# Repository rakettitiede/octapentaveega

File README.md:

# OctaPentaVeega

Fun hobby project to generate 32 x 16 characters of text on VGA output (or alternatively 64x64 pixel graphics, or split-screen graphics/text) from Attiny85 with 6x10 pixel font.

Data is read from UART at 9600bps. [Subset of ANSI escapes is supported](https://github.com/Jartza/octapentaveega/blob/master/vga_uart_protocol.txt).

Wiring 3 Attinys together gets you 8 color output :)

Links:
* <a href="https://www.youtube.com/watch?v=G1QWNDck0yU" target="_blank">Video: Ansi tester 8-color (ansitester.py)</a>
* <a href="https://www.youtube.com/watch?v=Vw5xGuLFy8Q" target="_blank">Video: Ansi tester Black & White (ansitester.py)</a>
* <a href="https://www.youtube.com/watch?v=YL0RwEtTN70" target="_blank">Video: Graphics mode (tricoder) & left scroll</a>
* <a href="https://www.youtube.com/watch?v=1iC2AHI5caI" target="_blank">Video: Full screen scroll (B/W)</a>
* <a href="https://www.youtube.com/watch?v=936m7FMS__c" target="_blank">Video: Full screen scroll (8-color)</a>
* <a href="https://drive.google.com/file/d/0B2dTzW9TMeBxN29YOVFsZFJ2Sm8/view?usp=sharing&resourcekey=0-qg94SZRgscnID9sQj7wqgg" target="_blank">Video: Multiple individual rows scroll (B/W)</a>
* <a href="https://drive.google.com/file/d/0B2dTzW9TMeBxQ1luNFhwcXl3QjA/view?usp=sharing&resourcekey=0-P5mUCc9mNvyFCUTxm9JVWQ" target="_blank">Picture: 6x10 pixel font</a>
* <a href="https://drive.google.com/file/d/0B2dTzW9TMeBxRzJOQVZMNFE0STg/view?usp=sharing&resourcekey=0-tbPVQ-RSZv2ljsOSo7lrrg" target="_blank">Picture: Generic (B/W)</a>

Board photos:
* <a href="https://drive.google.com/file/d/0B2dTzW9TMeBxaFFxam1uVW05NlE/view?usp=sharing&resourcekey=0-hj-EZfwC4E2AGv0eFjva1Q" target="_blank">B/W board</a>
* <a href="https://drive.google.com/file/d/0B2dTzW9TMeBxRXVzSUNCT1h2NHM/view?usp=sharing&resourcekey=0-VIRaT1kCkgjpB7zByPp_LA" target="_blank">8-color board</a>
* <a href="https://drive.google.com/file/d/0B2dTzW9TMeBxX2VmQmw3aXhWUDA/view?usp=sharing&resourcekey=0-ecXRcLez51cEmPnjZG1DXQ" target="_blank">8-color board back</a>
* <a href="https://drive.google.com/file/d/0B2dTzW9TMeBxUDQ4QUduWDV2TFE/view?usp=sharing&resourcekey=0-0n-sL1mumwSXGCBFCg1Kcg" target="_blank">Arduino shield, 8-color with level shifter (3.3 / 5v compatible)</a>

<p>

//Jartza

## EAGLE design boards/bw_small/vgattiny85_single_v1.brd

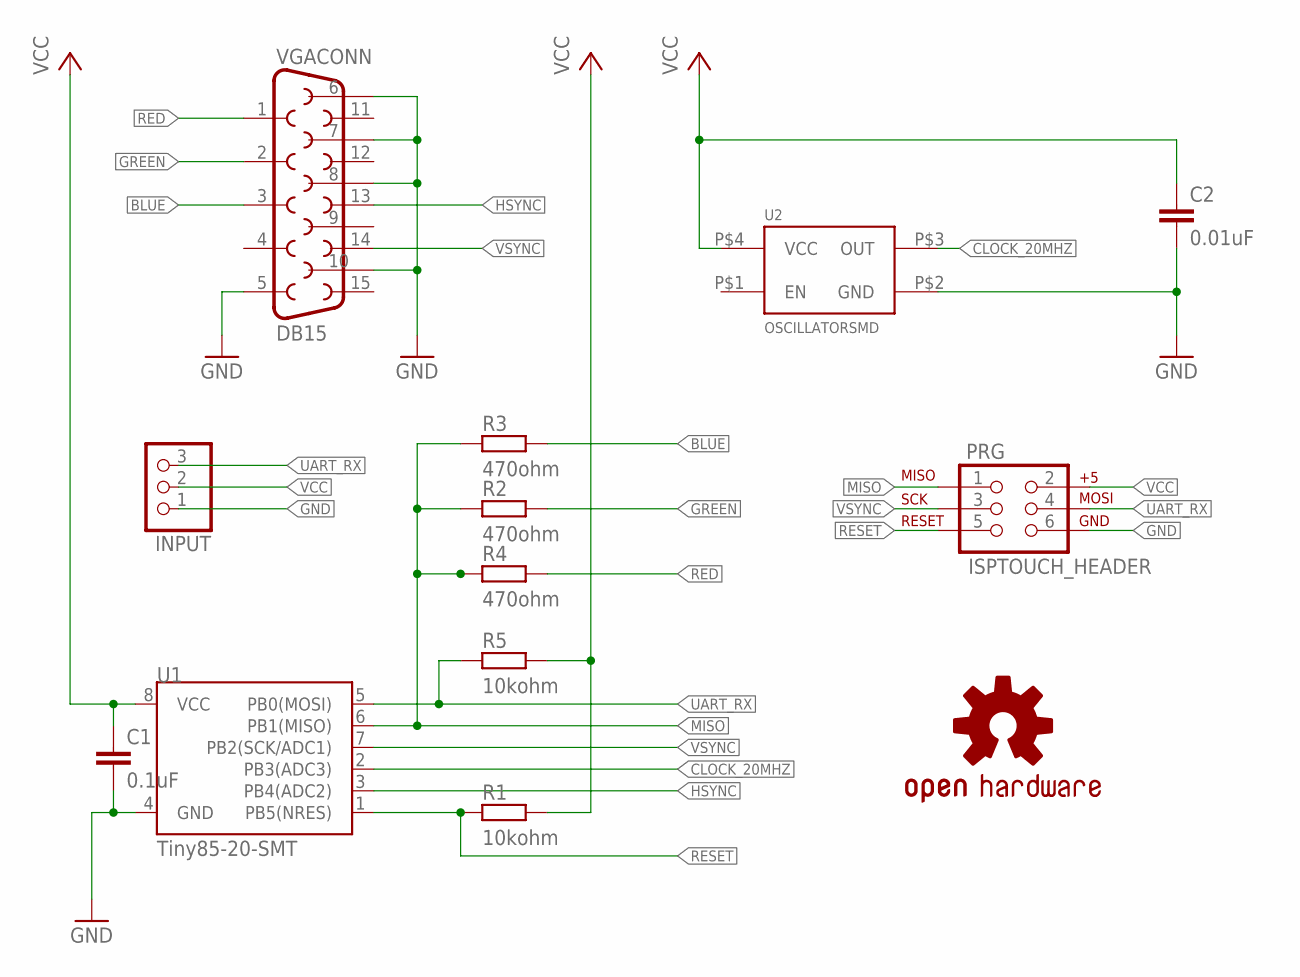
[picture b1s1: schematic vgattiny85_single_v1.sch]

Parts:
C1: 0.1uF; 0603-CAP
C2: 0.01uF; 0603-CAP
INPUT: PINHD-1X03_2.54-S; 1X03-S
LOGO1: OSHW-LOGOS; OSHW-LOGO-S
PRG: ISPTOUCH_HEADER; AVX_9188_6-WAY_MATING_GUIDE
R1, R5: 10kohm; R0603
R2, R3, R4: 470ohm; R0603
U1: Tiny85-20-SMT; SO08-EIAJ
U2: OSCILLATORSMD; CRYSTAL-SMD-7X5
VGACONN: DB15

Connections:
BLUE: R3.2, VGACONN.3
CLOCK_20MHZ: U1.2 (PB3(ADC3)), U2.P$3 (OUT)
GND: C1.2, C2.2, INPUT.1, PRG.6, U1.4 (GND), U2.P$2 (GND), VGACONN.5, VGACONN.6, VGACONN.7, VGACONN.8, VGACONN.10
GREEN: R2.2, VGACONN.2
HSYNC: U1.3 (PB4(ADC2)), VGACONN.13
MISO: PRG.1, R2.1, R3.1, R4.1, U1.6 (PB1(MISO))
RED: R4.2, VGACONN.1
RESET: PRG.5, R1.1, U1.1 (PB5(NRES))
UART_RX: INPUT.3, PRG.4, R5.1, U1.5 (PB0(MOSI))
VCC: C1.1, C2.1, INPUT.2, PRG.2, R1.2, R5.2, U1.8 (VCC), U2.P$4 (VCC)
VSYNC: PRG.3, U1.7 (PB2(SCK/ADC1)), VGACONN.14

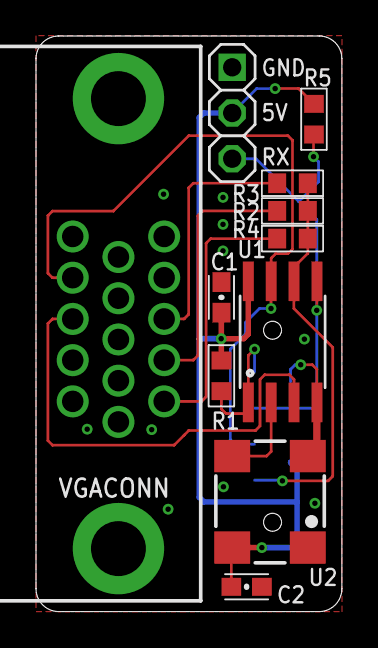
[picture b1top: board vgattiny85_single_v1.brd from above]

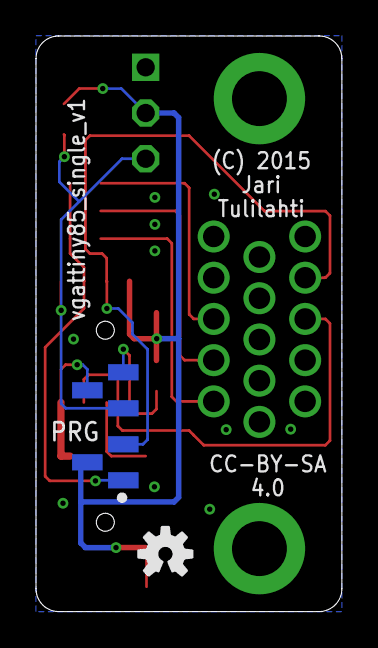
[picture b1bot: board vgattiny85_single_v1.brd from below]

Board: 2 copper layers, 17.0 x 32.0 mm, 13 parts (2 on the bottom side), 11 nets.

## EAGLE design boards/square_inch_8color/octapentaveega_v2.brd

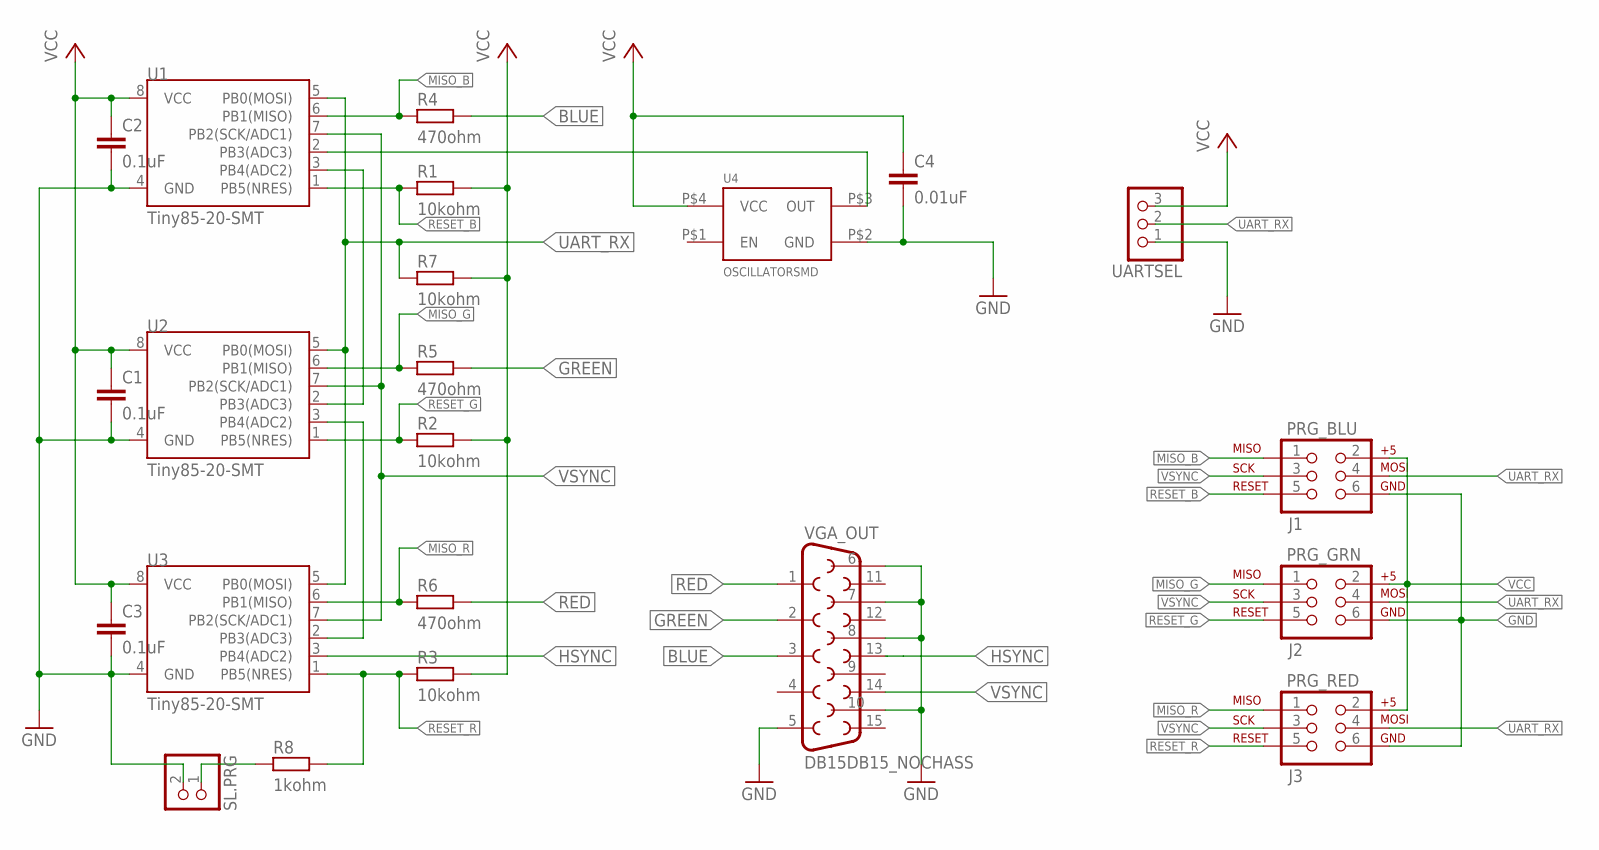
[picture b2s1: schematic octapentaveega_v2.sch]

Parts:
C1, C2, C3: 0.1uF; C0603
C4: 0.01uF; C0603
PRG_BLU: J1; AVX_9188_6-WAY_MATING_GUIDE
PRG_GRN: J2; AVX_9188_6-WAY_MATING_GUIDE
PRG_RED: J3; AVX_9188_6-WAY_MATING_GUIDE
R1, R2, R3, R7: 10kohm; R0603
R4, R5, R6: 470ohm; R0603
R8: 1kohm; R0603
SL.PRG: PINHD-1X02_2.54-S; 1X02-S
U1, U2, U3: Tiny85-20-SMT; SO08-EIAJ
U4: OSCILLATORSMD; CRYSTAL-SMD-7X5
UARTSEL: PINHD-1X03_2.54-S; 1X03-S
VGA_OUT: DB15DB15_NOCHASS; DB15_NOCHASS

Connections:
BLUE: R4.2, VGA_OUT.3
GND: C1.2, C2.2, C3.2, C4.2, PRG_BLU.6, PRG_GRN.6, PRG_RED.6, SL.PRG.2, U1.4 (GND), U2.4 (GND), U3.4 (GND), U4.P$2 (GND), UARTSEL.1, VGA_OUT.5, VGA_OUT.6, VGA_OUT.7, VGA_OUT.8, VGA_OUT.10
GREEN: R5.2, VGA_OUT.2
HSYNC: U3.3 (PB4(ADC2)), VGA_OUT.13
MISO_B: PRG_BLU.1, R4.1, U1.6 (PB1(MISO))
MISO_G: PRG_GRN.1, R5.1, U2.6 (PB1(MISO))
MISO_R: PRG_RED.1, R6.1, U3.6 (PB1(MISO))
unnamed: U1.2 (PB3(ADC3)), U4.P$3 (OUT)
unnamed: U1.3 (PB4(ADC2)), U2.2 (PB3(ADC3))
unnamed: U2.3 (PB4(ADC2)), U3.2 (PB3(ADC3))
unnamed: R8.1, SL.PRG.1
RED: R6.2, VGA_OUT.1
RESET_B: PRG_BLU.5, R1.1, U1.1 (PB5(NRES))
RESET_G: PRG_GRN.5, R2.1, U2.1 (PB5(NRES))
RESET_R: PRG_RED.5, R3.1, R8.2, U3.1 (PB5(NRES))
UART_RX: PRG_BLU.4, PRG_GRN.4, PRG_RED.4, R7.1, U1.5 (PB0(MOSI)), U2.5 (PB0(MOSI)), U3.5 (PB0(MOSI)), UARTSEL.2
VCC: C1.1, C2.1, C3.1, C4.1, PRG_BLU.2, PRG_GRN.2, PRG_RED.2, R1.2, R2.2, R3.2, R7.2, U1.8 (VCC), U2.8 (VCC), U3.8 (VCC), U4.P$4 (VCC), UARTSEL.3
VSYNC: PRG_BLU.3, PRG_GRN.3, PRG_RED.3, U1.7 (PB2(SCK/ADC1)), U2.7 (PB2(SCK/ADC1)), U3.7 (PB2(SCK/ADC1)), VGA_OUT.14

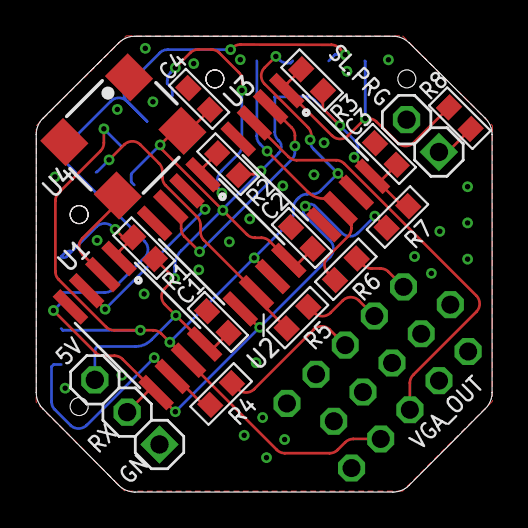
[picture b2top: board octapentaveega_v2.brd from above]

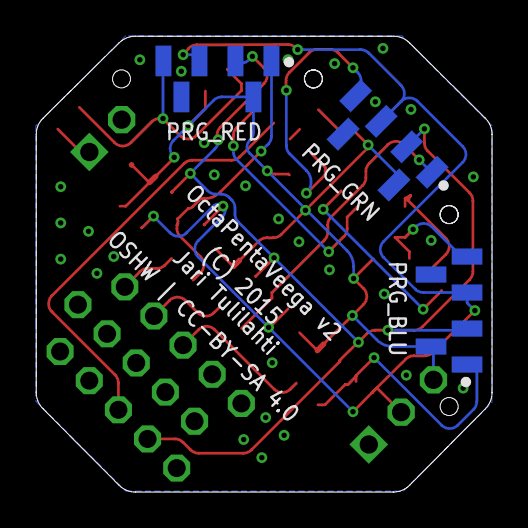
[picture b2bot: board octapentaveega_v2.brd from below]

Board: 2 copper layers, 25.3 x 25.3 mm, 22 parts (3 on the bottom side), 18 nets.

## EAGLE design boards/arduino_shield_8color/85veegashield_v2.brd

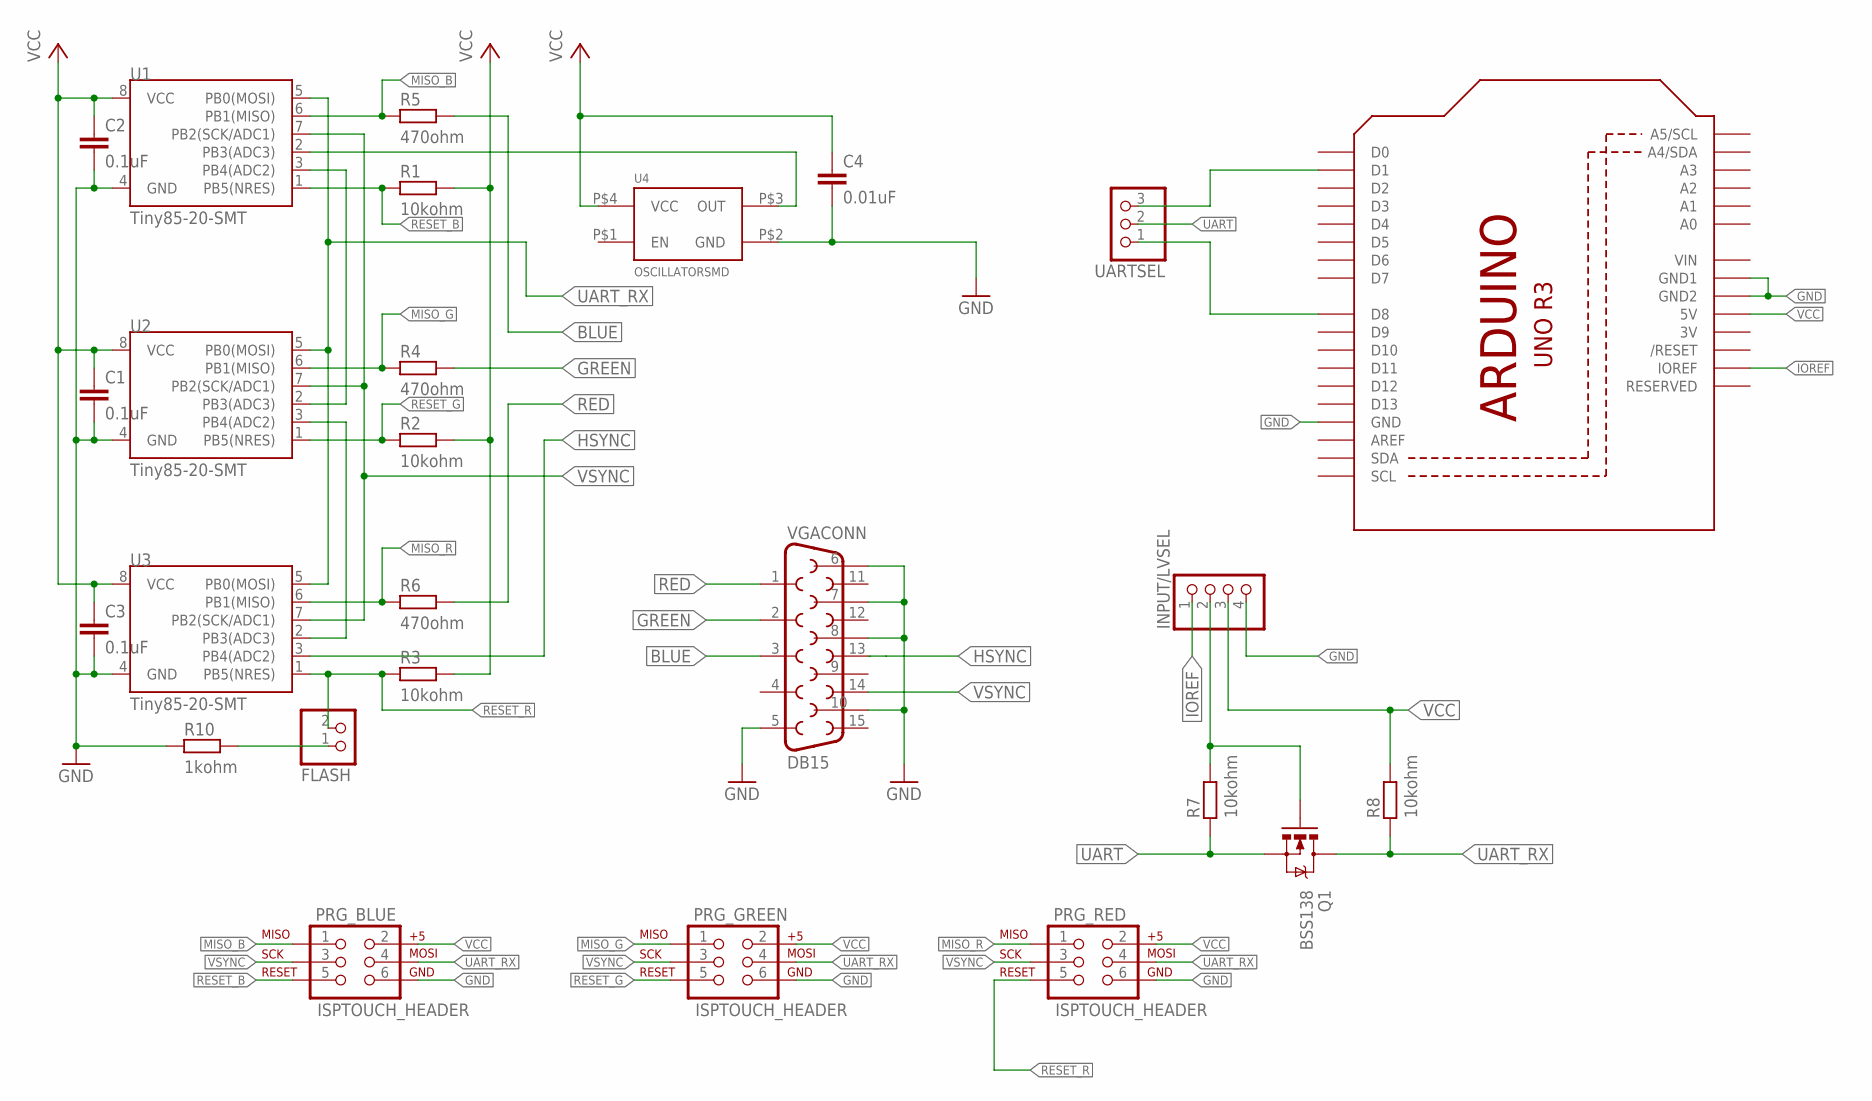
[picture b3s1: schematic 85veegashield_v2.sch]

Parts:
C1, C2, C3: 0.1uF; 0603-CAP
C4: 0.01uF; 0603-CAP
FLASH: PINHD-1X02_2.54-S; 1X02-S
INPUT/LVSEL: PINHD-1X04_2.54-S; 1X04-S
PRG_BLUE: ISPTOUCH_HEADER; AVX_9188_6-WAY_MATING_GUIDE
PRG_GREEN: ISPTOUCH_HEADER; AVX_9188_6-WAY_MATING_GUIDE
PRG_RED: ISPTOUCH_HEADER; AVX_9188_6-WAY_MATING_GUIDE
Q1: BSS138; SOT23
R1, R2, R3, R7, R8: 10kohm; R0603
R4, R5, R6: 470ohm; R0603
R10: 1kohm; R0603
U1, U2, U3: Tiny85-20-SMT; SO08-EIAJ
U4: OSCILLATORSMD; CRYSTAL-SMD-7X5
U$1: ARDUINOR3-DIMENSION; ARDUINOR3
UARTSEL: PINHD-1X03_2.54-S; 1X03-S
VGACONN: DB15

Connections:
3V: U$1.3V
BLUE: R5.2, VGACONN.3
FOO: INPUT/LVSEL.2, Q1.1 (G), R7.2
GND: C1.2, C2.2, C3.2, C4.2, INPUT/LVSEL.4, PRG_BLUE.6, PRG_GREEN.6, PRG_RED.6, R10.1, U1.4 (GND), U2.4 (GND), U3.4 (GND), U4.P$2 (GND), U$1.GND, U$1.GND1, U$1.GND2, VGACONN.5, VGACONN.6, VGACONN.7, VGACONN.8, VGACONN.10
GREEN: R4.2, VGACONN.2
HSYNC: U3.3 (PB4(ADC2)), VGACONN.13
IOREF: INPUT/LVSEL.1, U$1.IOREF
MISO_B: PRG_BLUE.1, R5.1, U1.6 (PB1(MISO))
MISO_G: PRG_GREEN.1, R4.1, U2.6 (PB1(MISO))
MISO_R: PRG_RED.1, R6.1, U3.6 (PB1(MISO))
unnamed: U1.2 (PB3(ADC3)), U4.P$3 (OUT)
unnamed: U1.3 (PB4(ADC2)), U2.2 (PB3(ADC3))
unnamed: U2.3 (PB4(ADC2)), U3.2 (PB3(ADC3))
unnamed: U$1.D1, UARTSEL.3
unnamed: FLASH.1, R10.2
unnamed: U$1.D8, UARTSEL.1
RED: R6.2, VGACONN.1
RESET_B: PRG_BLUE.5, R1.1, U1.1 (PB5(NRES))
RESET_G: PRG_GREEN.5, R2.1, U2.1 (PB5(NRES))
RESET_R: FLASH.2, PRG_RED.5, R3.1, U3.1 (PB5(NRES))
UART: Q1.2 (S), R7.1, UARTSEL.2
UART_RX: PRG_BLUE.4, PRG_GREEN.4, PRG_RED.4, Q1.3 (D), R8.1, U1.5 (PB0(MOSI)), U2.5 (PB0(MOSI)), U3.5 (PB0(MOSI))
VCC: C1.1, C2.1, C3.1, C4.1, INPUT/LVSEL.3, PRG_BLUE.2, PRG_GREEN.2, PRG_RED.2, R1.2, R2.2, R3.2, R8.2, U1.8 (VCC), U2.8 (VCC), U3.8 (VCC), U4.P$4 (VCC), U$1.5V
VIN: U$1.VIN
VSYNC: PRG_BLUE.3, PRG_GREEN.3, PRG_RED.3, U1.7 (PB2(SCK/ADC1)), U2.7 (PB2(SCK/ADC1)), U3.7 (PB2(SCK/ADC1)), VGACONN.14

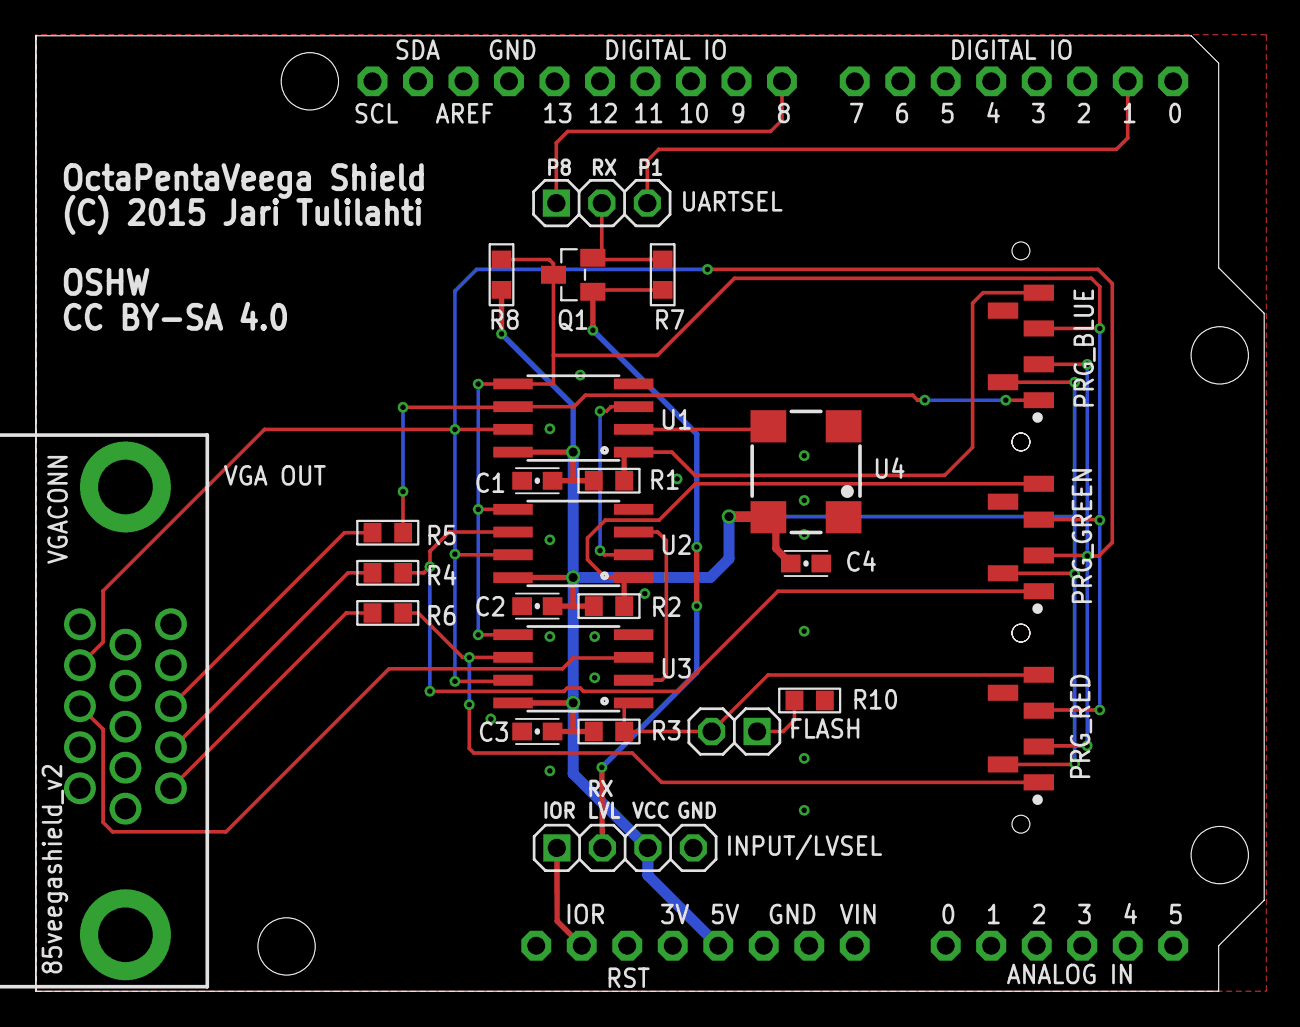
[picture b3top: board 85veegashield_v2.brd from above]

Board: 2 copper layers, 68.6 x 53.3 mm, 26 parts (0 on the bottom side), 23 nets.

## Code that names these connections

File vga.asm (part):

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
; Pins used for different signals
;
.equ UART_PIN           = PB0
.equ RGB_PIN            = PB1
.equ VSYNC_PIN          = PB2
.equ HSYNC_PIN          = PB4

; General purpose IO registers used as storage
;
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        ;
.ifdef VGA_MASTER

        sbi DDRB, HSYNC_PIN             ; Master drives both HSYNC
        sbi DDRB, VSYNC_PIN             ; and VSYNC
.else
        cbi DDRB, VSYNC_PIN             ; Slave sync to VSYNC, set as input
        sbi PORTB, VSYNC_PIN            ; Enable pull-up
.endif
        sbi DDRB, RGB_PIN
        cbi DDRB, UART_PIN
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        cp vline_lo, temp               ; Low
        cpc vline_hi, one               ; High
        brne check_vsync_high
        cbi PORTB, VSYNC_PIN            ; Vsync low
        rjmp wait_uart

check_vsync_high:
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        cp vline_lo, temp               ; Low
        cpc vline_hi, one               ; High
        brne check_vlines
        sbi PORTB, VSYNC_PIN            ; Vsync high
        rjmp wait_uart
.endif

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
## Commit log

2015-07-02 Init
2015-07-02 RM stupid files
2015-07-04 First working version
2015-07-05 Testing testing
2015-07-05 Magic test
2015-07-05 Add fonts
2015-07-05 Leeloo Dallas Multiline
2015-07-05 59.9Hz
2015-07-07 Update font numbers
2015-07-07 Not working
2015-07-07 Start moving to assembler
2015-07-07 Sync pulses from ASM
2015-07-07 Testing
2015-07-07 ASM white pic
2015-07-07 Working again with Z
2015-07-07 Pixels drawing with asm
2015-07-07 Finally working the same way as C
2015-07-07 ASM. Finally checkerboard again
2015-07-08 modeline.txt deleted online with Bitbucket
2015-07-08 Add gitignore
2015-07-09 Finally, first time text on screen. YAY.
2015-07-09 New font
2015-07-09 Updated font and texts
2015-07-09 Fix compile warnings
2015-07-09 More cycles
2015-07-09 More nops
2015-07-09 19+9 cycles now free
2015-07-09 Remove unnecessary files
2015-07-09 28 clock cycles to spend while hsync...
2015-07-09 Add warning to main
2015-07-09 Fix merge
2015-07-09 Fix merge #2
2015-07-09 Fix typo
2015-07-09 Fix comments
2015-07-09 Increase comments
2015-07-10 Add fuses for external clock
2015-07-11 Add delay
2015-07-11 Testing multicolor
2015-07-11 Testing more
2015-07-24 PWM testing
2015-07-24 Test
2015-07-24 Revert "Test"
    This reverts commit 2e156631ab2d2208e27d0f607dd578b39eb0d12a.
2015-07-25 Shave off clock cycles
2015-08-02 Lotta fixes
2015-08-02 Fix formatting
2015-08-02 Add attiny85 include
2015-08-02 Add copyright comment
2015-08-02 We don't need no stinking vectors :)
2015-08-03 Small optimization
2015-08-03 Temp commit
2015-08-03 Avra has bugs :(
2015-08-03 Optimize more
2015-08-03 Better centered display
2015-08-03 Testing UART
2015-08-03 Ahh. Small timing fix and everything works
2015-08-03 Somehow working makefile for avra
2015-08-04 Add HEX file for those who don't want to compile themselves
2015-08-05 Add spec-draft of UART commands to be implemented
2015-08-05 ISNA :)
2015-08-07 Add some comments
2015-08-07 Clear screen quick'n'dirty version
2015-08-07 Better clear
2015-08-08 Much simpler, glitch-free screen clearing
2015-08-08 Prevent double-clearing during screen-clear
2015-08-08 Fix indent, remove clear_mode and insert general state bitfield-register instead
2015-08-08 Add .lst
2015-08-08 Updated font
2015-08-08 Slight change to font
2015-08-08 Slight change to font #2
2015-08-08 Fix screen clear
2015-08-09 Prepare for ANSI codes by reserving registers
2015-08-09 Add comment
2015-08-09 Some changes to free up registers
2015-08-09 Renumber and organize registers
2015-08-09 Simplify UART
2015-08-09 Enhance clearing
2015-08-10 Small comment change
2015-08-10 Create LICENSE
2015-08-10 Update license
2015-08-10 Scrolling support
2015-08-10 Scroll enhance
2015-08-10 swap instead of lsl
2015-08-12 Scrolling yay
2015-08-13 Make scroll simpler (and save clocks) by unrolling loop...
2015-08-13 Unrolled scroll clear
2015-08-13 Separate CR and LF
2015-08-13 Hawk-eye-Arttu spotted a bug
2015-08-13 Handle CR and LF the same
2015-08-13 ANSI parser creation started
2015-08-14 Preliminary support for cursor move with ANSI
2015-08-14 Fix cursor move
2015-08-14 Optimize cursor move
2015-08-14 Cursor movement with scrolling too
2015-08-14 Reorganize code
2015-08-14 Fix color value setting
2015-08-14 ISNA update
2015-08-14 Say something about ANSI
2015-08-14 Rename file
2015-08-14 Rename back
2015-08-14 Small fixes to ANSI code parsing. Also added enable/disable wrap code
2015-08-14 Update ANSI escape documentation
2015-08-14 Update font
2015-08-14 Slight font fix
2015-08-14 Rewrite ANSI color setting code
2015-08-14 Add 'schematics'
2015-08-14 Update schematics
2015-08-14 Update schematics #2
2015-08-16 Update doc
2015-08-16 Makefile ready for red, green, blue.... COLORS
2015-08-16 Add font.py
2015-08-17 Add slaves and synchronization. Yay.
2015-08-17 Reverse fuse and flashing order
2015-08-17 Add backspace support
2015-08-18 Fix font
2015-08-21 Makefile comment
2015-08-21 Increase delay in slaves
2015-08-22 Fix bug in color handling
2015-08-22 Don't try to generate hsync in slaves
2015-08-22 Add ANSI tester python code
2015-08-22 ASCII Schematics
2015-08-22 Tiny mod
2015-08-23 Fix bug in schematics
2015-08-23 Add cap to schematics
2015-08-23 Add VGA connector to schematics
2015-08-23 Update connector diagram
2015-08-23 Update connector diagram #2
2015-08-23 Update ansitester
2015-08-23 Update Picture link
2015-08-25 Add .hex files for all colors
2015-09-08 Small change to ansidemo
2015-09-08 Put .hex files back
2015-09-10 Ansitester add text effect
2015-09-12 Shorten lines
2015-10-23 Enable pull-up
2015-10-26 Font generator added
2015-10-26 Font generator filename fix
2015-10-27 Update hex
2015-10-27 Upate Makefile to generate font
2015-10-27 Add copyright to font definition
2015-10-27 Nice reduce by aspect added
2015-10-27 Font generator enhancement
2015-10-27 Add character names to font definitions
2015-10-30 Enable pull-ups
2015-10-30 Rename UART doc
2015-10-30 ESC ESC
2015-10-30 Start fixing UART doc
2015-10-30 UART doc table
2015-10-30 Revert "UART doc table"
    This reverts commit 4f61a6cebca707a01b4579eb6891bbc2ecd14280.
2015-10-30 Change back
2015-11-04 Fix for python 3.x
2015-11-04 Slight fix for formatting
2015-11-04 Ansi tester xrange->range
2015-11-04 Fix comment
2015-11-05 Commit fix
2015-11-05 Fix ansitester
2015-11-05 Oops, indent error in ansitester
2015-11-07 Update Video URL
2015-11-09 Better initialization
2015-11-09 Fix wrap mode control characters
2015-11-09 Add comments to USI
2015-11-09 Fix ansitester wrap
2015-11-09 Final fix for wrap-mode escape code
2015-11-10 Preliminary support for row-scroll
2015-11-10 Scroll left
2015-11-10 Update ANSI doc
2015-11-10 Update font data comments
2015-11-10 Add another video link to README
2015-11-11 Add resistor to schematics for Flashing jumper
2015-11-11 Modify ansitester for shorter line length
2015-11-11 Update schematics into ditaa-compatible and generate png
2015-11-11 Make schematics render more nicely with ditaa
2015-11-11 Make schematics render more nicely with ditaa #2
2015-11-12 improve schematics with ditaa
2015-11-12 improve schematics with ditaa #2
2015-11-12 improve schematics with ditaa #3
2015-11-12 improve schematics with ditaa #4
2015-11-12 Add schematics to README
2015-11-12 Add UART as argument for ansitester
2015-11-12 Change project name in README
2015-11-12 Update schematics URL in README
2015-11-14 Fix Ansitester.py with flush
2015-11-15 Started adding documentation
2015-11-15 Add comment to hsync and vsync pic, small typo change
2015-11-16 Add HSYNC timings
2015-11-16 Split microseconds to two rows in HSYNC timings doc
2015-11-16 Add VSYNC timings
2015-11-16 Update documentation images
2015-11-16 Enhance hsync/vsync relation chart
2015-11-16 Add colors to hsync-vsync diagram
2015-11-16 Switch front and back porches in hsync
2015-11-16 Modified by comments from Mitch :)
2015-11-16 Align continuation dots
2015-11-17 Fix typo in vsync/hsync diagram
2015-11-17 Add Hsync and Vsync general diagram
2015-11-17 Minor doc fix
2015-11-17 Truncate some lines
2015-11-17 Trunate diagram lines
2015-11-17 Some more trimming of diagram pics
2015-11-17 Add final diagram with RGB
2015-11-17 Slight mod to RGB diagram
2015-11-17 Add voltage levels to RGB
2015-11-17 Add blanking area to general concept
2015-11-18 Oops. Hsync pulse is 3.81us, not 38.1us
2015-11-18 Slight mods
2015-11-18 Diagrams done for now
2015-11-18 More accurate pixel time
2015-11-29 Preliminary left scroll support
2015-11-29 Left scroll
2015-11-30 Better scrolling
2015-11-30 Slight fixes to left scroll
2015-11-30 Maybe a bit better left scroll
2015-11-30 Couldn't fix the minor glitches in scroll... have to re-check later
2015-11-30 Don't increase row number if not full-screen-scrolling
2015-12-01 No more UART chars missing while scrolling
2015-12-01 Even better left scrolling without lost UART characters
2015-12-01 Get lost .hex files back
2015-12-01 Max out scroll at 255
2015-12-01 Max out full-screen scroll at 32 columns
2015-12-01 Update scroll to doc
2015-12-01 Mod ansitester
2015-12-02 Update Video link
2015-12-02 Add BW picture to readme
2015-12-02 Only scroll once in ansitester
2015-12-06 No lost characters after left scroll... finally, yay
2015-12-06 Update scroll docs
2015-12-08 Add left scroll tester
2015-12-08 Add row-scroll-tester
2015-12-09 Add scroller for B/W
2015-12-19 First somehow working version of 32x16 character full-memory-bloat
2015-12-19 Add .hex files back
2015-12-19 Resync master and servants
2015-12-19 Enhance font a bit
2015-12-19 Preliminary support for left scroll - with small glitches
2015-12-19 Small font fix
2015-12-19 Font, fix q
2015-12-19 Vertical scroll fixed
2015-12-19 Horizontal scroll fixed
2015-12-19 Remove unused state
2015-12-19 Small fix to ansitester.py
2015-12-19 Finetuning the horizontal scrolling a bit
2015-12-20 Tiny bugfix of scroll
2015-12-20 Fix hex
2015-12-20 Add PCBs. Eagle files + Gerbers
2015-12-20 Remove .DS_Store files
2015-12-20 Add font pic
2015-12-20 Slightly fixing various stuff
2015-12-20 Graphics mode testing
2015-12-20 Add rude graphics mode tester
2015-12-20 Add pixel font generator
2015-12-20 Add .hex back
2015-12-21 Update Makefile for pixel generator
2015-12-21 Re-sync slaves again :)
2015-12-21 Horizontal scroll slight change
2015-12-21 Graphics friendly fixes
2015-12-21 Add Euro symbol back to font
2015-12-21 Fine-tune front- and back-porch
2015-12-22 Add 'pixel font' too
2015-12-22 Preliminary support for 'tricoder' mode
2015-12-23 Fix for tricoder
2015-12-23 Optimize scroll by sigle cycle
2015-12-23 Fix optimization bug
2015-12-23 Update ansitester and README
2015-12-25 Add full-reset command
2015-12-27 Add tricode to docs
2015-12-29 Flawless left scroll
2015-12-30 Add schematics and hex files
2015-12-30 Grow last pixel a bit to be in line with others
2015-12-30 Update README, small changes
2015-12-30 Add full charset displayer to tests
2015-12-31 Add one more scroller for testing
2016-01-20 Programmer change
2016-03-10 Store ANSI codes as characters
2016-03-18 Update ANSI escape docs
2016-05-24 Update copyright years
2016-05-24 One more 2016 updated
2017-02-26 One more test
2017-05-05 Latest hex files
2018-12-16 Indent with spaces
2022-05-11 Add pics
2022-05-11 Update links in README

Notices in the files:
vga.asm:
(C) Copyright 2015-2016 Jari Tulilahti
Licensed under the Apache License, Version 2.0 (the "License");
boards/arduino_shield_8color/85veegashield_v2.brd:
(C) 2015 Jari Tulilahti
CC BY-SA 4.0
boards/bw_small/vgattiny85_single_v1.brd:
CC-BY-SA
boards/square_inch_8color/octapentaveega_v2.brd:
OSHW | CC-BY-SA 4.0
parts and their libraries:
SparkFun-DigitalIC: Licensing: CC v3.0 Share-Alike You are welcome to use this library for commercial purposes.
